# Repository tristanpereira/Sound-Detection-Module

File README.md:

# Sound-Detection-Module
A simple circuit that uses an electret microphone to detect sound and output an analog signal. 
Uses a non-inverting Op-amp circuit to amplify the voltage from the electret mic such that it can be read by microcontrollers such as a 
Raspberry Pi or Arduino. 

This repository contains the schematic and pcb files for the circuit.

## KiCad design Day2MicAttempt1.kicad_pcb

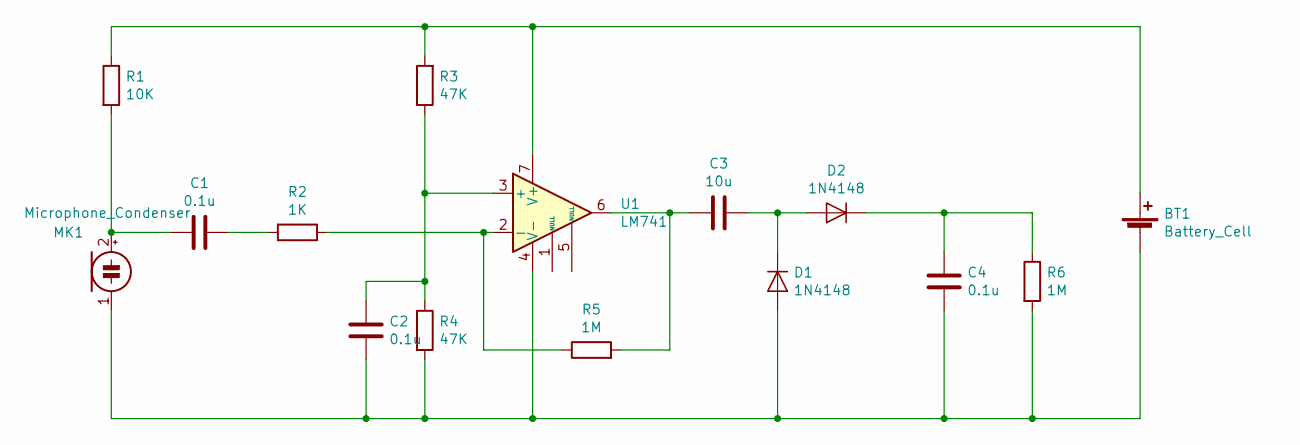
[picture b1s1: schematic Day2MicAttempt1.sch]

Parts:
BT1: Battery_Cell; TerminalBlock_Altech_AK300-2_P5.00mm
C1, C2, C4: 0.1u; CP_Axial_L10.0mm_D4.5mm_P15.00mm_Horizontal
C3: 10u; CP_Axial_L11.0mm_D5.0mm_P18.00mm_Horizontal
D1, D2: 1N4148; D_DO-35_SOD27_P7.62mm_Horizontal
MK1: Microphone_Condenser; PinSocket_1x02_P2.54mm_Vertical
R1: 10K; R_Axial_DIN0204_L3.6mm_D1.6mm_P5.08mm_Horizontal
R2: 1K; R_Axial_DIN0204_L3.6mm_D1.6mm_P5.08mm_Horizontal
R3, R4: 47K; R_Axial_DIN0204_L3.6mm_D1.6mm_P5.08mm_Horizontal
R5, R6: 1M; R_Axial_DIN0204_L3.6mm_D1.6mm_P5.08mm_Horizontal
U1: LM741; DIP-8_W7.62mm_LongPads

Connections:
unnamed: BT1.1 (+), R1.1, R3.2, U1.7 (V+)
unnamed: BT1.2 (-), C2.2, C4.2, D1.2 (A), MK1.1 (-), R4.2, R6.2, U1.4 (V-)
unnamed: C1.1, R2.2
unnamed: C1.2, MK1.2 (+), R1.2
unnamed: C2.1, R3.1, R4.1, U1.3 (+)
unnamed: C3.1, D1.1 (K), D2.2 (A)
unnamed: C3.2, R5.2, U1.6
unnamed: C4.1, D2.1 (K), R6.1
unnamed: R2.1, R5.1, U1.2 (-)

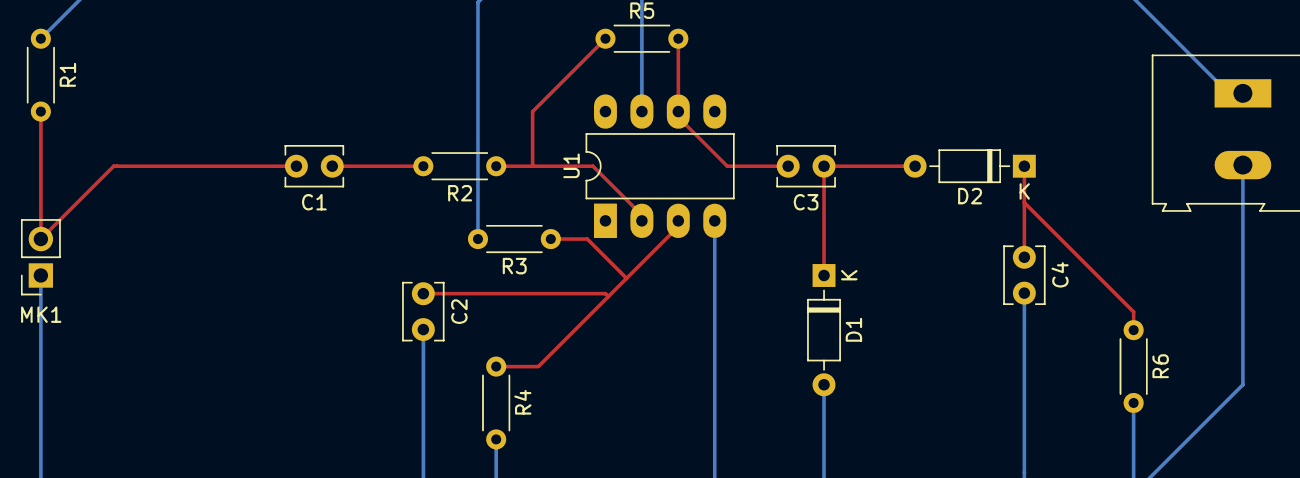
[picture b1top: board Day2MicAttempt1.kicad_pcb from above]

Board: 2 copper layers, 15 parts (0 on the bottom side), 9 nets.
